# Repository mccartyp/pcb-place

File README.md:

# pcb-place repository

This repository contains complementary command-line tools for reviewable PCB
planning and placement workflows. The architecture separates concerns:
**`pcb-plan` extracts facts, the AI (Claude) generates design intent, and
`pcb-place` executes intent.** A third tool, **`pcb-schgen`**, generates a
readable KiCad schematic (`.kicad_sch`) from a netlist, `board.pln`, and a placed
board — closing the gap where Zener/pcb produces a netlist and PCB but no
schematic.

```text
KiCad PCB + netlist + stackup + board dimensions
  -> pcb-plan inspect       (extract board intelligence -> planning-hints/)
  -> Claude generates board.pln   (authoritative design intent, AI-authored)
  -> pcb-plan check / validate
  -> pcb-plan emit          (board.pln -> placement.ppl)
  -> pcb-place              (deterministic execute -> reports)
  -> Claude optimization loop     (analyze reports, edit board.pln, repeat)
```

- [`pcb-plan`](src/pcb_plan/README.md) is a **board-intelligence extractor** and
  `board.pln` reviewer. Its `inspect` command extracts facts (geometry,
  connectivity) and *candidate hints* (roles, functional paths, power islands,
  edge connectors, mechanicals, RF zones) into a `planning-hints/` directory for
  AI planning. It also reviews, validates (`check`), updates, and emits
  deterministic `placement.ppl` from `board.pln`.
- The AI (Claude) is the **primary planning engine**: it turns `planning-hints/`
  into `board.pln`, the authoritative design-intent document, and iterates on it
  using placement/routing/simulation reports.
- [`pcb-place`](src/pcb_place/README.md) is the **deterministic placement
  executor**. It consumes `placement.ppl`, applies/reflows/optimizes footprint
  placement, validates placement rules, writes placed KiCad `.kicad_pcb` files,
  and reports.
- [`pcb-schgen`](docs/pcb-schgen.md) is the **deterministic schematic
  generator**. It consumes the netlist, the placed board, and `board.pln`, and
  writes a connectivity-correct, readable `.kicad_sch` (local circuits wired,
  rails as power symbols/labels, parts grouped by functional intent) plus a
  generation report and symbol map. It never modifies `pcb-plan`, `pcb-place`,
  or the PCB.

The split is intentional. `pcb-plan inspect` must **not** place components,
create placement ownership, build topology clusters heuristically, or infer a
final floorplan — those are AI planning problems solved in `board.pln`.
`pcb-plan` must not move footprints or route traces; `pcb-place` must not infer
planning strategy, power islands, or a final floorplan. KiCad groups are exported
as metadata only and must never drive placement.

## Repository structure

```text
.
├── README.md                  # Repository overview and structure
├── pyproject.toml             # Packaging and console-script metadata
├── src/
│   ├── pcb_plan/
│   │   ├── README.md          # pcb-plan and board.pln documentation
│   │   ├── __init__.py        # Import package for console scripts
│   │   ├── pcb_plan.py        # pcb-plan implementation
│   │   └── pcb_plan_facades/  # Internal migration/facade modules
│   ├── pcb_place/
│   │   ├── README.md          # pcb-place DSL and executor documentation
│   │   ├── __init__.py        # Import package for console scripts
│   │   └── pcb_place.py       # pcb-place implementation
│   └── pcb_schgen/
│       ├── __init__.py        # Import package for console scripts
│       └── pcb_schgen.py      # pcb-schgen implementation
├── docs/
│   └── pcb-schgen.md          # pcb-schgen documentation
├── examples/                  # Example placement workflows and inputs
└── tests/                     # Unit and CLI integration tests
```

There are no root-level `pcb_plan.py` or `pcb_place.py` compatibility entry
points and no hyphenated tool directories under `src/`. The canonical
executable implementations live beside their READMEs in the importable packages
`src/pcb_plan/` and `src/pcb_place/`, which also provide the normal Python entry
point targets for installed console scripts.

## Overall workflow

`pcb-plan` and `pcb-place` fit after generated board creation and before manual
routing/review:

```text
Zener / Diode pcb design
    ↓
pcb build
    ↓
pcb layout
    ↓
pcb-plan inspect        (extract facts -> planning-hints/)
    ↓
Claude generates board.pln   (AI is the primary planning engine)
    ↓
pcb-plan check          (validate intent)
    ↓
Claude review/optimization
    ↓
pcb-plan emit
    ↓
placement.ppl
    ↓
pcb-place
    ↓
placed KiCad board + reports
    ↓
Claude optimization loop (edit board.pln, repeat)
    ↓
manual high-speed review / routing / DRC
```

A conservative command-line workflow is:

```bash
pcb build board.zen
pcb layout board.zen

# 1. Extract board intelligence into planning-hints/ (facts + candidate hints).
pcb-plan inspect \
  --board layout.kicad_pcb \
  --netlist default.net \
  --width 75 --height 75 \
  --out planning-hints

# 2. Let Claude generate board.pln from planning-hints/ (see planning-hints/
#    ai-pln-prompt.md). board.pln is the authoritative design-intent document:
#    mechanical/edge constraints, regions, power islands, high-speed corridors,
#    functional paths, ownership, routing/SI, stackup, and simulation triggers.
#    The pcb-bootstrap Claude skill drives this step.

# (Legacy heuristic alternative: pcb-plan init writes a first-pass board.pln.)
pcb-plan init \
  --board layout.kicad_pcb \
  --netlist default.net \
  -o board.pln \
  --report-json pcb-plan-init-report.json

# Let Claude review/optimize board.pln before emit. Typical fixes include
# board geometry, regions, keepouts, edge_required/access_side metadata,
# DecouplingArray/PullupArray strategy, differential pairs, routing/SI
# constraints, and OpenEMS/ngspice triggers.

pcb-plan check \
  --pln board.pln \
  --board layout.kicad_pcb \
  --netlist default.net \
  --report-json pcb-plan-check-report.json

# Let Claude review/optimize pcb-plan-check-report.json.

pcb-plan emit \
  --pln board.pln \
  --board layout.kicad_pcb \
  --netlist default.net \
  -o placement.ppl

pcb-place layout.kicad_pcb placement.ppl --dry-run \
  --report-json pcb-place-report.json
# Let Claude review/optimize pcb-place-report.json and feed fixes back to
# board.pln rather than hand-editing placement.ppl when possible.
pcb-place layout.kicad_pcb placement.ppl -o layout.placed.kicad_pcb
pcbnew layout.placed.kicad_pcb
```

Concise AI-assisted workflow:

1. Extract facts and candidate hints with `pcb-plan inspect` into
   `planning-hints/`.
2. Let Claude generate `board.pln` from `planning-hints/` (the authoritative,
   AI-authored design-intent document). The `pcb-bootstrap` skill drives this.
3. Validate intent with `pcb-plan check`, then generate `placement.ppl` with
   `pcb-plan emit`.
4. Apply with `pcb-place` after reviewing the dry-run report.
5. Iterate using placement, routing, DRC/ERC, OpenEMS, and ngspice reports,
   feeding fixes back into `board.pln` (the optimization surface).

Run `pcb-plan check` after `init`/`update` and before `emit` to catch
low-confidence plans (missing nets, mostly-singleton clusters, mostly-unplaced
components, duplicate rules, missing differential pairs, rejected `Series(...)`
inferences, or footprint-extents board geometry) before generating
`placement.ppl`. AI review should prefer `board.pln` intent edits over manual
`placement.ppl` hacks and should preserve provenance for inferred changes. See
[`src/pcb_plan/README.md`](src/pcb_plan/README.md) for the `plan_confidence`
model and the `--strict-confidence`/`--allow-low-confidence` flags on `emit`.

For early use, you can skip the planner and write `placement.ppl` by hand, or
run the planner with only a KiCad board:

```bash
pcb-plan emit --board layout.kicad_pcb -o placement.ppl
pcb-place layout.kicad_pcb placement.ppl -o layout.placed.kicad_pcb
```

When initializing `board.pln` before Edge.Cuts are reliable, pass explicit board geometry so generated regions and edge-aware placements use the intended outline:

```bash
pcb-plan init --board layout.kicad_pcb --width 75 --height 75 -o board.pln
```

Legacy one-shot planner invocation is still supported for compatibility:

```bash
pcb-plan --board layout.kicad_pcb --netlist default.net --intent board.pln -o placement.ppl
```

## Board intelligence extraction: `pcb-plan inspect`

`pcb-plan inspect` is the entry point of the AI planning workflow. It is a
board-intelligence **extractor**, not a floorplanner: it reads facts and emits
*candidate hints* for an AI (or human) to turn into an authoritative
`board.pln`.

```bash
pcb-plan inspect \
  --board layout.kicad_pcb \
  --netlist default.net \
  --width 75 --height 75 \
  --out planning-hints
```

It writes a `planning-hints/` directory:

```text
planning-hints/
  board-hints.json                 # master facts + candidate hints
  board-hints.md                   # human-readable summary
  component-table.csv              # per-component facts (role, bbox, nets)
  connectivity-graph.json          # component/net graph + ownership hints
  footprint-bboxes.json            # bbox, centroid, area per component
  pad-locations.json               # absolute/local pad coordinates and nets
  candidate-functional-paths.json  # connector -> protection -> IC paths
  candidate-power-islands.json     # regulator + hot-loop topology
  candidate-high-speed-paths.json  # high-speed subset of functional paths
  candidate-edge-connectors.json   # access side / auto-rotation / edge_required hints
  candidate-mechanicals.json       # mounting-hole corner assignments
  candidate-rf-zones.json          # RF antenna keepout candidates
  routing-classes.json             # candidate routing classes (impedance needs fab stackup)
  ai-pln-prompt.md                 # prompt to help Claude generate board.pln
  ai-placement-review.md           # checklist for reviewing board.pln vs hints
```

`pcb-plan inspect` must **not** attempt final placement, create topology
clusters heuristically, create placement ownership automatically, or infer a
final floorplan. Everything it emits is a candidate hint and is marked as such.
KiCad groups are exported under `imported_kicad_groups` with `metadata_only:
true` and **must not drive placement** — they are preserved for information only.

`board.pln` is the authoritative design-intent document. It is generated
primarily by AI from `planning-hints/` and contains mechanical constraints,
edge-required components, connector orientation/access sides, placement regions,
power islands, high-speed corridors, functional paths, ownership, routing
classes, SI constraints, stackup, and simulation triggers. The AI optimization
loop primarily edits `board.pln` (preferred), then `placement.ppl` overrides,
then manual `Anchor()` as a last resort. See the
[`pcb-bootstrap`](skills/pcb-bootstrap/SKILL.md) skill for generating it.

## Tool responsibilities

### pcb-plan: extract facts and review intent

`pcb-plan` extracts board intelligence (`inspect`), reviews and validates the
AI-authored `board.pln`, and emits a readable `.ppl` placement plan (`emit`). It
may infer *candidate* roles such as connectors, ICs, decoupling capacitors, ESD
devices, high-speed differential interfaces, RF modules, power regulators,
pullups, and series passives — as hints, not authoritative placement decisions.

`pcb-plan` no longer invents the floorplan: the AI generates `board.pln` from
the hints. `pcb-plan inspect` output and `board.pln` are meant to be reviewed,
AI-optimized, edited, diffed, validated with `check`, and emitted. `pcb-plan`
does **not** place components, route traces, tune differential pairs, validate
impedance, certify EMI behavior, or claim production readiness.

Planner quality depends on real board geometry and connectivity. Explicit
`board.pln` geometry overrides KiCad `Edge.Cuts`, and `Edge.Cuts` overrides the
last-resort footprint-extents fallback. Supplying a netlist lets `pcb-plan` build
multi-member connectivity clusters, infer differential pairs, and place support
passives with semantic helpers such as `Decoupling`, `NearPad`, `ESD`, `Pullup`,
`Series`, `Satellite`, and `Between`; review any `unplaced_components` in the
report.

See [`src/pcb_plan/README.md`](src/pcb_plan/README.md) for planner CLI details,
`board.pln` syntax, provenance, reports, routing/SI hooks, simulation hooks,
heuristics, and limitations.

### pcb-place: execute placement intent

`pcb-place` reads an explicit `.ppl` part-placement file and applies
deterministic footprint-level placement updates to a KiCad `.kicad_pcb` file. It
provides dry-run, check, validation, reporting, alias import, board-geometry
handling, keepout/region validation, and safe atomic writes.

Executor behavior should remain predictable and independent of planner
heuristics. It does **not** infer placement strategy from netlists and does
**not** route traces.

See [`src/pcb_place/README.md`](src/pcb_place/README.md) for the placement DSL,
safety checks, CLI reference, and executor-specific examples.

## Topology-aware placement model

Placement planning and execution follow a fixed priority model:

```text
mechanical constraints first
functional signal path topology second
power topology third
support passives fourth
spacing/clearance always enforced
high-speed/EMI best practices baked into scoring
```

### Groups vs clusters vs ownership

Groups are metadata. A component may belong to several semantic groups at once
(a retimer cluster, an HDMI path, a 1V2 power domain, a decoupling group), but
**final placement ownership is explicit and unique**: exactly one rule owns each
ref's final coordinates. Clusters only preserve coarse neighborhoods; they are
never atomic placement units, and a later higher-priority rule (ESD, power
island member, decoupling array, near-pad) refines members out of the cluster
move. `pcb-plan` reports this as `ownership_model` / `semantic_groups` /
`multi_group_components`; `pcb-place` reports the final winner per ref in
`ownership` and notes every cluster move that a refinement overrode.

Ownership priority (highest first): explicit fixed/locked mechanical,
edge-required connector, explicit anchor, functional-path placement
(ESD/Between/Series), DecouplingArray/NearPad, PullupArray, Satellite, cluster
fallback.

### Mechanical constraints first

Mounting holes are fixed/corner mechanical objects, never cluster members. If
`board.pln` defines `mechanical.mounting_holes`, those corners/locations win;
otherwise `pcb-plan` keeps holes that already sit at distinct corners and
redistributes clustered/colocated holes to distinct corners (`inset` 3 mm) with
a review warning. Board outline, keepouts (RF antenna, cable access), and edge
connectors are planned before any other component.

### Edge-required components

Connectors that leave the board (HDMI, USB, RJ45/Ethernet, DC jacks, card
slots) are inferred — or declared in `board.pln` — as `edge_required`. They are
edge-locked, never pulled inward by optimization, and rotated by access side:

```yaml
components:
  J1:
    role: hdmi_connector
    edge_required: true
    access_side: left
    allow_body_outside_board: true
    locked: true
    rotation: auto
```

`rotation: auto` uses the convention that at rot=0 the footprint's mating face
points toward the top board edge (-y), so auto maps top→0°, right→90°,
bottom→180°, left→270°; supply an explicit rotation when a footprint uses a
different convention. With `allow_body_outside_board: true` the connector body
or courtyard may extend past the board outline (an expected mechanical
condition, not an ordinary outside-board violation) while the footprint anchor
must stay on the board. Support parts stay inside the board unless explicitly
allowed.

### Functional paths and high-speed/EMI scoring

`pcb-plan` builds functional paths from the connectivity graph
(connector → ESD/protection → receiver/retimer) and emits them as
`HighSpeedPath(...)` declarations; `board.pln` `functional_paths:` entries pin
them explicitly. Paths reserve direct corridors before low-speed support parts
are placed: unrelated components are penalized out of corridors during
candidate scoring, and `pcb-place --high-speed-review` writes
`high-speed-placement-review.md` scoring each path for directness/straightness,
flow-through ESD position (protection belongs near the connector), corridor
intruders, and warnings requiring human review.

### Power islands and power/EMI scoring

Regulator sections are planned as topology-aware power islands, not generic
"power component piles": input capacitor tight to the regulator power pins,
inductor and output capacitor compact against the regulator, feedback network
at the FB pin away from the switch node — while downstream load decouplers stay
owned by their loads. `board.pln` `power_islands:` entries pin membership
explicitly. `pcb-place --power-review` writes `power-placement-review.md`
scoring cap/inductor distances, estimated hot-loop area, feedback proximity,
and separation from high-speed paths.

### Spacing profiles

Both tools default to a conservative, non-touching spacing profile and accept a
`board.pln` `spacing:` override:

```yaml
spacing:
  passive_to_passive: 0.25
  passive_to_ic: 0.40
  ic_to_ic: 0.75
  connector_to_component: 1.00
  mechanical_to_component: 1.00
```

Spacing is enforced during candidate scoring and validation. Arrays whose
requested pitch cannot satisfy clearance escalate their spacing instead of
emitting touching parts.

### Stackup profiles

`board.pln` supports reusable stackup templates for 2/4/6/8/10 layers:
`2_layer_basic`, `4_layer_signal_gnd_pwr_signal`, `6_layer_high_speed`,
`8_layer_high_speed`, `10_layer_high_speed`. A bare `stackup: { layers: 6 }`
expands to the conservative 6-layer profile and is marked
`source: stackup_template`, `confidence: medium`, `requires_review: true`.
Templates set layer roles, likely reference planes, and preferred high-speed
layers to improve placement/routing intent only — **controlled impedance always
requires the actual fabricator stackup**, and the tools emit a warning saying
so.

### AI-adjustable .pln and .ppl files

The `.pln` and `.ppl` files are intended to be edited by humans and AI
assistants as part of an iterative layout optimization workflow:

```text
generate board.pln  ->  AI reviews/edits board.pln  ->  pcb-plan emits placement.ppl
->  AI reviews/edits placement.ppl if needed  ->  pcb-place applies placement
->  reports feed back into board.pln
```

Generated files carry stable ordering for diffs, section comments explaining
inferred constraints (effective sides, edge requirements, paths, islands,
arrays), and provenance/`requires_review` markers. Both CLIs emit
`ai-edit-hints.md` (`pcb-plan emit --ai-edit-hints`, `pcb-place
--ai-edit-hints`) listing uncertain placement choices, low-confidence
constraints, multi-group components, placement owners, suggested `.pln`/`.ppl`
edits, and risks requiring engineering review.

### Why human review remains required

Placement-level heuristics and scoring cannot verify impedance, return paths,
reference-plane continuity, plane splits, thermal behavior, RF detuning, or
EMI compliance. The review reports exist to focus engineering attention, not to
replace it.

## Performance and runtime budgets

`pcb-place` uses bounded, staged search so placement stays fast even on dense
boards. A ~100-component board completes in a few seconds in the default
`normal` mode; it never runs unbounded.

### Optimization levels

Choose the search breadth/quality trade-off with `--optimization-level`:

| Level    | Candidates/rule | Reflow depth        | Post-legal probing | Use when |
|----------|-----------------|---------------------|--------------------|----------|
| `fast`   | 150             | local + group only  | accept first legal | quick iteration, CI smoke runs |
| `normal` | 500 (default)   | up to support region| small extra probe  | default placement |
| `deep`   | 2000            | up to parent move   | full search        | debug / exhaustive optimization |

`fast` does no parent reflow and accepts the first legal layout; `normal` is
balanced; `deep` searches harder and reflows more (and is slower by design).

### Time budget and best-effort timeout

`--time-budget-seconds N` (default `60`, `0` disables) bounds wall-clock time.
When the budget expires the placer does **not** abort: it keeps placing the
remaining components with the best known candidate, marks them
`requires_review`, records `timed_out: true`, and continues. Only `--strict`
turns a timeout into a hard error.

```bash
pcb-place board.kicad_pcb placement.ppl \
  --optimization-level normal \
  --time-budget-seconds 60 \
  --max-candidates-per-rule 500 \
  --max-floorplan-iterations 5
```

The placement report includes a `runtime` block:

```json
"runtime": {
  "optimization_level": "normal",
  "elapsed_seconds": 2.17,
  "budget_seconds": 60.0,
  "timed_out": false,
  "candidates_evaluated": 196,
  "cache_hits": 201176,
  "max_candidates_per_rule": 500,
  "degraded_refs": []
}
```

### Spatial index

Collision and clearance checks query a uniform-grid spatial index (stdlib only)
so each candidate is compared against only the handful of footprints near it
instead of every part on the board. The index updates as parts move and is
reported under `spatial_index`:

```json
"spatial_index": {
  "enabled": true,
  "cells": 93,
  "queries": 6382,
  "average_candidates_checked": 0.85
}
```

`average_candidates_checked` stays well below the part count — that is the
difference between local queries and a naive all-pairs scan.

### Bounded, staged search

For each placement primitive the search is bounded and staged:

- **Coarse → fine.** A limited set of high-quality candidates is generated and
  ranked; expensive checks run only on finalists.
- **Pruning.** Candidates that obviously cannot place (outside board/region,
  overlapping the expanded parent bbox, violating a hard keepout) are rejected
  before collision scoring.
- **Early success.** Once an *excellent* legal candidate is found (score under
  the level's threshold), the search stops instead of chasing a marginally
  better one.
- **Caps.** `--max-candidates-per-rule` caps evaluations per primitive so a
  single rule can never explode into thousands of checks. Legality always wins
  over the cap: the spacing-escalation ladder is never cut short before a legal
  placement is found.

### Reflow levels

Reflow is local by default, escalating only as needed (low-priority blockers —
testpoints, LEDs, straps, pullups, passives — move before critical parts; edge-
required and mechanically locked parts never move):

```text
level 0  local primitive only
level 1  same array/group
level 2  same parent support region
level 3  same functional island/path
level 4  adjacent regions
level 5  parent IC movement
```

`fast` uses levels 0–2, `normal` 0–3 (parent movement only when local placement
is impossible and the parent is movable), `deep` 0–5.

### Profiling

`--profile-placement profile.json` writes per-rule runtime, candidate counts,
collision-check counts, spatial-index stats, cache hit/miss, reflow attempts,
and the slowest rules — the data needed to tune a slow board:

```bash
pcb-place board.kicad_pcb placement.ppl --profile-placement profile.json
```

### Progress output

`--progress` prints concise, throttled per-rule progress to stderr for long
runs, e.g. `placing 34/102 C19 DecouplingArray candidates=120 elapsed=8.2s`.

## Installation

From the repository root:

```bash
pip install .
```

For development:

```bash
pip install -e '.[dev]'
pytest
```

The installed console scripts are:

```bash
pcb-plan --help
pcb-place --help
pcb-schgen --help
```

## Safety model

Both tools are sidecars around KiCad files:

- `pcb-plan` never writes directly to `.kicad_pcb`; it reads or writes
  `board.pln`, emits `placement.ppl`, and can emit JSON/Markdown reports plus
  routing/simulation planning artifacts.
- `pcb-place` rewrites only matched footprint-level placement records and
  defaults to writing a separate output file unless `--in-place` is explicitly
  requested.
- Generated or executed placement must be reviewed in KiCad before routing and
  fabrication.
- High-speed routing, impedance, return paths, reference planes, DRC/ERC,
  manufacturability, thermal behavior, RF behavior, and EMI compliance remain
  engineering responsibilities.

## Documentation map

- [`src/pcb_plan/README.md`](src/pcb_plan/README.md): planner-specific
  documentation for `board.pln`, lifecycle commands, routing/SI constraints,
  simulation hooks, reports, and `.ppl` generation.
- [`src/pcb_place/README.md`](src/pcb_place/README.md): executor-specific
  documentation for applying `.ppl` files to KiCad boards.
- [`docs/pcb-schgen.md`](docs/pcb-schgen.md): `pcb-schgen` schematic-generation
  CLI, inputs, wire-vs-label policy, reports, and KiCad compatibility.
- [`examples/`](examples): example placement workflows and input files.
- [`tests/`](tests): unit and CLI integration tests for both tools.

## Claude Skills

[`skills/`](skills) contains Claude Code skills that teach Claude how to drive
this repository's tools:

- [`skills/pcb-plan/SKILL.md`](skills/pcb-plan/SKILL.md) — `board.pln` and
  `placement.ppl` lifecycle: init, AI-assisted optimization, check, review,
  explain, update, emit, routing/SI constraints, stackup, differential pairs,
  simulation hooks, provenance.
- [`skills/pcb-place/SKILL.md`](skills/pcb-place/SKILL.md) — applying and
  debugging `placement.ppl` against a `.kicad_pcb` board: dry-run report
  review, validation, collisions/spacing/keepouts/regions, array diagnostics,
  edge-required movement attempts, troubleshooting.
- [`skills/pcb-automation-orchestrator/SKILL.md`](skills/pcb-automation-orchestrator/SKILL.md) —
  end-to-end AI iteration across `pcb-plan`, `pcb-place`, routing, DRC/ERC,
  and optional OpenEMS/ngspice simulation, including review, assisted, and
  bounded autonomous modes plus all-net and high-speed routing modes.

Short workflow: generate `board.pln`, let Claude review/optimize it, generate
`placement.ppl`, apply with `pcb-place`, and iterate using reports. Use
`pcb-plan` to own `board.pln`, use `pcb-place` to apply/debug the emitted
`placement.ppl` against a KiCad board, and use `pcb-automation-orchestrator`
to coordinate the full init/check/edit/emit/place/route/verify/simulate/update
loop. See [`skills/README.md`](skills/README.md) for details on when to use
each.

### Placement regions, support arrays, and edge-required parts

`pcb-place` models grouped support-part placement with an internal `PlacementRegion`: a legal strip on the left, right, top, or bottom of the expanded parent footprint bbox, clipped to board bounds and any strict `Region(...)` requested by the rule. `DecouplingArray(...)` and `PullupArray(...)` use these regions for capacity planning before selecting a scored candidate.

For arrays near a board edge, pcb-place computes the full array bounding box and slides it along the side tangent before rejecting it. Top/bottom arrays slide in X; left/right arrays slide in Y. Placement search reports include `placement_region`, capacity fields, `original_array_bbox`, `slid_array_bbox`, `slide_applied`, `slide_dx`, and `slide_dy`. Use `--explain-placement REF` to print the recorded winning score, candidate regions, slide data, and top rejected candidates for a specific part.

Board, region, keepout, and coordinate geometry accepts integral or floating-point values. For example, `Board(width=75, height=75)` and `Board(width=75.0, height=75.0)` are equivalent internally.

Edge-access components can be declared with metadata such as `edge_required=True`, `mechanical=True`, `locked=True`, and `access_side="left"` on `Edge(...)` placements. Edge-required anchors are treated as locked/high-priority owners; support components must move around them instead of pulling the connector or mechanical body inward. The generated report lists `edge_required_refs` separately from other locked refs.

Placement ownership precedence is enforced by priority and locking: fixed/locked/edge-required placements win over explicit anchors, pin-aware arrays, near-pad/satellite rules, and cluster fallback. When a cluster gives a coarse placement and a later DecouplingArray/PullupArray refines a support part, diagnostics report the refinement rather than silently fighting the rules.

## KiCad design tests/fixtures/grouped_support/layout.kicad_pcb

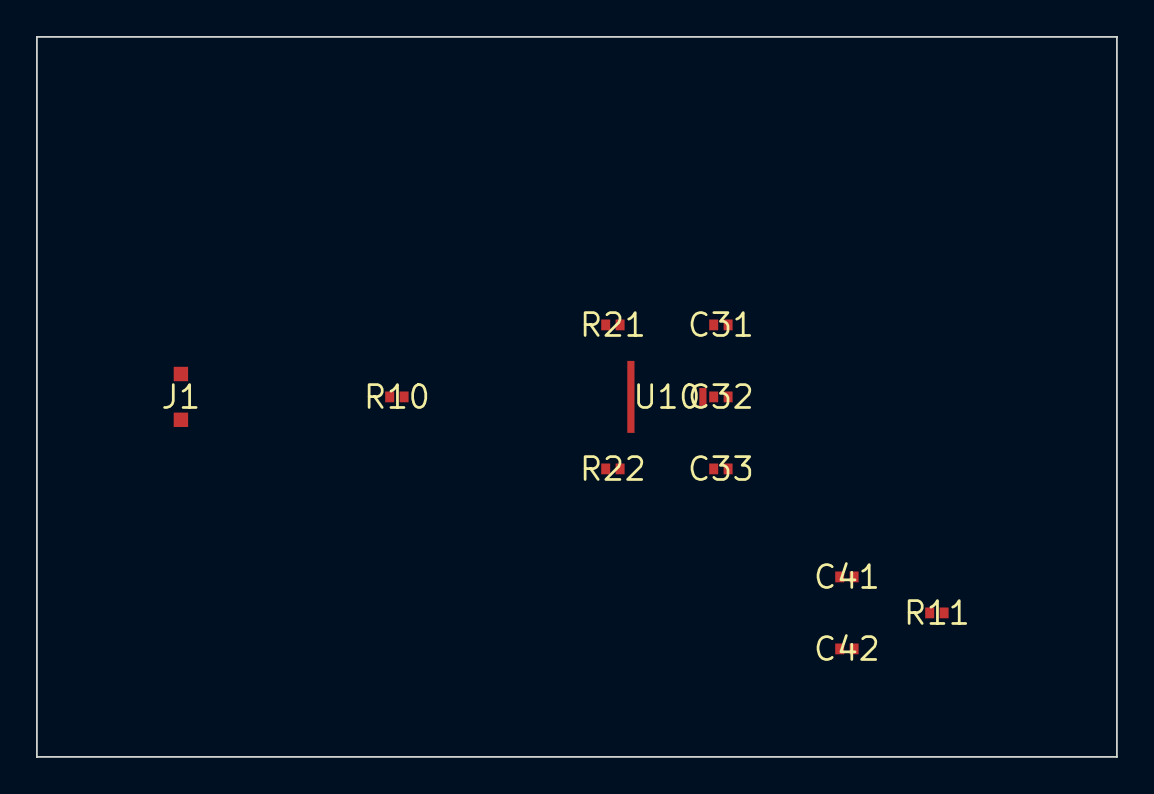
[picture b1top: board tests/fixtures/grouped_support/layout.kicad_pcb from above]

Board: 0 copper layers, 60.0 x 40.0 mm, 11 parts (0 on the bottom side), 8 nets, no tracks yet.

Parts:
C31, C32, C33: 100nF; C_0402
C41, C42: 1uF; C_0402
J1: CONN; PinHeader_1x02
R10: 33; R_0402
R11: 100; R_0402
R21, R22: 10k; R_0402
U10: MCU; QFN-40

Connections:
3V3: C31.1, C32.1, C33.1, R21.1, R22.1, U10.1
DATA: J1.1, R10.1
DATA2: R10.2, U10.5
FNET1: C41.1, R11.1
FNET2: C42.1, R11.2
GND: C31.2, C32.2, C33.2, J1.2, U10.2
SCL: R22.2, U10.4
SDA: R21.2, U10.3

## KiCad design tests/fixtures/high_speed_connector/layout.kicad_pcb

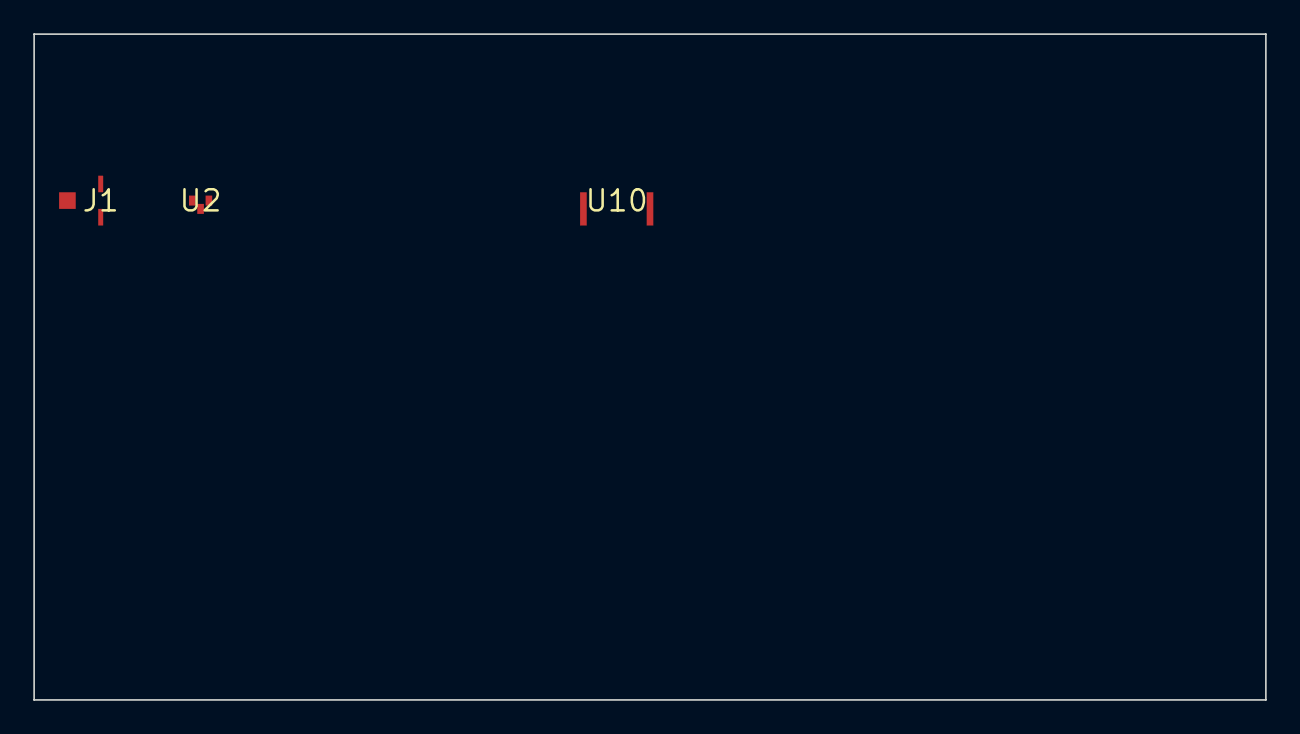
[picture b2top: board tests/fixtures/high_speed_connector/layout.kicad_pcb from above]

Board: 0 copper layers, 74.0 x 40.0 mm, 3 parts (0 on the bottom side), 3 nets, no tracks yet.

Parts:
J1: HDMI_IN; HDMI_A
U2: ESD; ESD_Array
U10: HDMI Retimer; QFN-40

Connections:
GND: J1.G, U2.3, U10.4
TMDS0_N: J1.2, U2.2, U10.2
TMDS0_P: J1.1, U2.1, U10.1

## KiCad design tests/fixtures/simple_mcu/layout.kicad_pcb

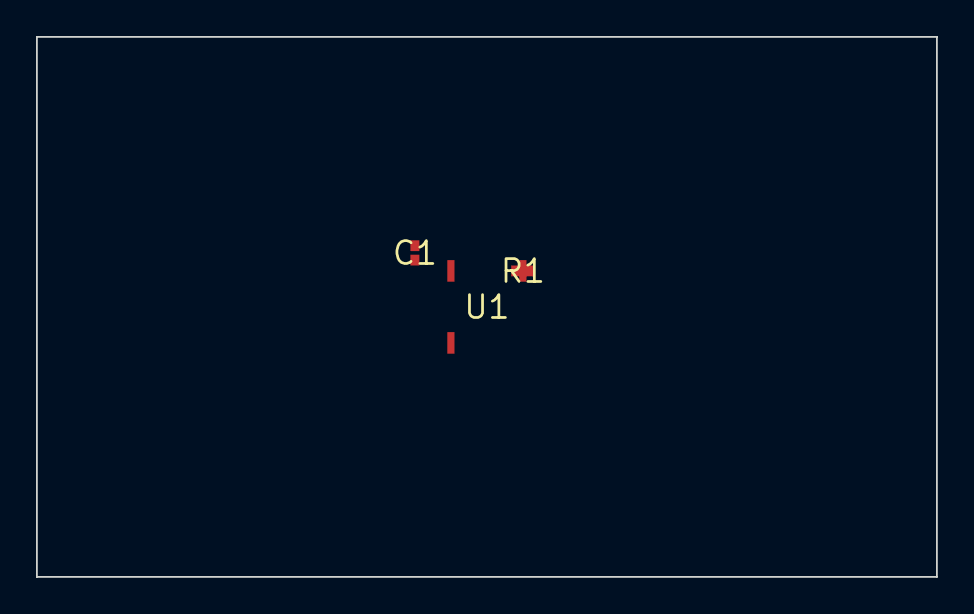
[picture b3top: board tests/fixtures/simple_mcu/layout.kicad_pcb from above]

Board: 0 copper layers, 50.0 x 30.0 mm, 3 parts (0 on the bottom side), 3 nets, no tracks yet.

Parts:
C1: 100nF; C_0402
R1: 10k; R_0402
U1: MCU; TQFP-32

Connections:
3V3: C1.1, R1.1, U1.1
BOOT0: R1.2, U1.3
GND: C1.2, U1.2

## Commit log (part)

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2026-06-10 Add Zener netlist alias resolution
2026-06-10 Filter suffix alias matches to existing footprints
2026-06-10 Make KiCad placement output safer
2026-06-10 Let dry-runs report unsafe placements
2026-06-10 Add board geometry and outline support
2026-06-10 Validate rectangular Edge.Cuts outlines
2026-06-11 Fix collision validation scope and board side handling
2026-06-11 Ensure tests include KiCad PCB fixture
2026-06-11 Include examples in source distribution
2026-06-11 Restore all minimal test fixtures when missing
2026-06-11 Fix generated UUID handling
2026-06-11 Deduplicate resolved cluster members
2026-06-11 Add planner-friendly placement primitives
2026-06-11 Honor planner placement overrides during search
2026-06-11 Document pln syntax reference
2026-06-11 Avoid overlapping synthesized RF keepouts
2026-06-11 Remove root compatibility entry points
2026-06-11 Add Claude skills for pcb-plan, pcb-place, and orchestrator workflows
    Adds skills/pcb-plan, skills/pcb-place, and
    skills/pcb-automation-orchestrator SKILL.md files plus skills/README.md,
    and links them from the root README under a new Claude Skills section.
    https://claude.ai/code/session_01GYvjSuXui5PLRL4NxjSqD3
2026-06-11 Standardize src package directory names
2026-06-11 Fix connector cluster edge-placement heuristic and Edge() top/bottom offset
    Edge() ignored y=/offset= for top/bottom edges, collapsing connectors
    placed on the same edge to a single point. The connector cluster
    heuristic also only distinguished left/right thirds of the board,
    never producing top/bottom edge placements, and force-snapped interior
    connectors to an edge even when that introduced large relocations or
    new overlaps. Pick the nearest of all four edges, only snap to an edge
2026-06-11 Make pcb-plan connectivity-aware
2026-06-12 Add search-based placement engine for robust NearPad/Satellite/Between
    Replace immediate-failure logic in NearPad, Satellite, Between, and
    cluster member placement with a generic candidate search engine that
    scores nearby legal positions by distance, clearance margin, and board
    edge proximity before giving up. Adds side="inward" for NearPad,
    alternate-side/perimeter search for Satellite, auto_spread for Between,
    cluster-local region search for soft members, a DecouplingArray()
2026-06-12 Add DecouplingArray/PullupArray primitives, pcb-plan check, and plan confidence gates
    pcb-place gains place_array_near_target() and the DecouplingArray()/
    PullupArray() primitives, which place a group of related parts as a
    single row near a parent (or pad), trying candidate sides, keeping the
    group together when it fits, and falling back to per-member
    search-based placement with diagnostics otherwise.
    pcb-plan now emits a single DecouplingArray()/PullupArray() rule for
2026-06-12 Add .gitignore for Python bytecode caches
2026-06-12 Fix decoupling array parent keepout placement
2026-06-12 Add scored placement candidate selection
2026-06-12 Add pcb-plan init board geometry options
2026-06-12 Slide arrays within strict placement regions
2026-06-12 docs: add AI-assisted pcb plan optimization workflow
2026-06-12 Make pcb-plan cluster member inference smarter, emit Edge.Cuts outline
    - Exclude power-net (not just ground-net) connectivity when pulling
    components into a cluster, so shared power rails no longer balloon
    cluster membership to nearly the whole board.
    - Cap all proximity-based and connectivity-based membership checks to
    the cluster radius so electrically-related but physically distant
    components aren't dragged into a rigidly-moved cluster.
2026-06-12 Gate emit_outline on trusted board geometry; require electrical link for connector cluster support parts
    emit_outline=True is no longer emitted when board geometry was inferred
    from footprint extents (low confidence), avoiding a synthetic Edge.Cuts
    outline that could cut through components. For connector clusters
    (proximity_any_role=False), nearby support-role passives are only swept
    into the rigidly-moved Edge() cluster if they share a signal/connection
    with the connector, preventing unrelated decoupling caps from being
2026-06-12 Redesign pcb-plan/pcb-place for topology-aware floorplanning and ownership
    Placement now follows a fixed priority model: mechanical constraints first,
    functional signal-path topology second, power topology third, support
    passives fourth, with spacing always enforced and high-speed/EMI practices
    baked into scoring.
    pcb-plan:
    - Mounting holes are fixed mechanical objects distributed to distinct
2026-06-13 Add constraint-driven iterative floorplanner with reflow and no-abort placement
    Treat a local placement failure as evidence the floorplan is suboptimal
    rather than a component problem. pcb-place now runs an iterative
    floorplanner that places, scores the global layout, reflows the worst
    constraints, and re-scores until convergence.
    Reflow ladder (before parking):
    - repack within the grouped-array search (existing)
2026-06-13 Route all primitive search failures through no-abort parking; demote parked validation
    Address two P1 review findings on the no-abort guarantee:
    1. NearPad / Satellite(side="auto") / Between performed their own candidate
    searches and raised PlacementError directly, bypassing reflow/parking. They
    now share _resolve_unplaceable_search(), which tries a Level-2 reflow and
    otherwise parks, so default best-effort placement no longer aborts on these
    primitives. Only strict/fail-fast raise.
2026-06-13 Fix board geometry regressions in pcb-plan and pcb-place
    Restore robust board geometry handling across the floorplanner:
    - Footprint-extents fallback now uses footprint bounding boxes (with a
    per-footprint at-position fallback) plus a 5 mm margin, so valid
    footprints never collapse to a zero-size board. Adds
    footprint_extents_bounds()/_footprint_abs_bbox() and a configurable
    margin (DEFAULT_FOOTPRINT_MARGIN_MM).
2026-06-13 Keep footprint-extents fallback invalid when there are no footprints
    Address review feedback: when a board has neither Edge.Cuts nor any
    parseable footprints, the 5 mm margin previously fabricated a valid-looking
    10x10 footprint_extents board that passed validation. The "never zero"
    guarantee only applies to valid footprints, so the empty case now stays
    zero-size and is rejected with the clear sourced error.
    - infer_geometry_from_footprints() returns zero-size geometry (no margin)
2026-06-13 Add bounded, staged placement search with spatial indexing and runtime budgets
    Placement runtime is now bounded and predictable: a ~100-component board that
    previously took minutes (and could approach 30+ minutes on dense layouts) now
    completes in a few seconds in the default normal mode.
    Core changes (pcb-place):
    - Spatial index: a stdlib uniform-grid index over placed footprint bboxes.
    Collision and clearance checks query only nearby parts instead of scanning
2026-06-13 Honor strict timeouts during searches
2026-06-13 Honor strict timeouts during searches
    ### Motivation
    - In strict mode a run that observes the budget expire during an expensive mid-search (e.g. grouped-array probing) only set `timed_out` and continued until the next rule, allowing a run to complete s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
    - Make timeout behavior consistent so any search path that detects an expired `RuntimeBudget` immediately raises when `strict=True`.
    ### Description
    - Add a shared helper method `PlacementEngine._raise_strict_timeout()` that raises a `PlacementError` when `self.runtime.strict` and the budget has expired.
    - Call the helper from `PlacementEngine._maybe_degrade_on_timeout()` to pres
2026-06-13 Clamp cluster member targets to board bounds
2026-06-13 Honor outside-board opt-out for cluster clamping
2026-06-13 Reduce CLI wrapper merge surface
2026-06-13 Avoid edge cluster support overlaps
2026-06-13 Avoid edge cluster support overlaps
    ### Motivation
    - Cluster moves previously attempted to drag locked non-anchor members and could place support parts on top of each other when an anchor was edge-required/locked, causing validation overlap errors.
    - The change aims to preserve explicit locked placements and to cause support parts in edge-required/locked clusters to spread to legal, non-overlapping locations.
    ### Description
    - In `src/pcb_place/pcb_place.py` the cluster placement loop now skips moving non-anchor members that are already locked, records a `locked_move_attempt`, and emits a warning message instead of attem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
    - The cluster placement now computes an `avoid_ov
2026-06-13 Avoid overlaps in cluster support placements
2026-06-14 Avoid overlaps for non-anchor cluster members and honor --allow-overlap
    ### Motivation
    - Cluster support parts that were listed alongside their anchor could remain coincident/overlapped even when global placement avoidance was enabled, causing validation failures for overlapping origin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
    ### Description
    - Add a `permissive_overlap` flag to `PlacementEngine` and wire it from the `allow_overlap` CLI/application option so `--allow-overlap` still relaxes avoidance when requested.\
    - Change cluster-placement logic so non-anchor members use the placement policy (`PlacementPolicy(avoid_overlap=True)`) to decide overlap avoi
2026-06-14 Floorplanner: fix vertical-edge span and honor keepouts
    Addresses two P1 review findings:
    - _edge_span used the board width for left/right edges, but connectors there
    are distributed along y, so the span must be the board height (and width for
    top/bottom). On a rectangular board this produced along-edge coordinates off
    the board; square boards masked it. Swap the dimensions.
    - compute_floorplan ignored declared keepouts, so the force-directed solve
2026-06-14 Floorplanner: handle tight boards and circular cluster membership
    Follow-up to the wirelength-driven floorplanner for smaller boards.
    - Split real-body (hard) extents from halo-inflated (soft) extents. The soft
    halo spreads parts for their support arrays when there is room; the hard
    pass guarantees real-footprint + clearance separation that pcb-place
    validates. Clamp parts by their real body so they can use the whole core.
    - Add a decompaction fallback: any part the pairwise relaxation wedges against
2026-06-14 Add pcb-plan inspect; pivot to extract -> AI plan -> execute architecture
    Convert pcb-plan from a heuristic floorplanner into a board-intelligence
    extractor that feeds AI-driven board.pln generation.
    - Add `pcb-plan inspect` command that writes a planning-hints/ directory of
    facts and candidate hints (board-hints.json/.md, component-table.csv,
    connectivity-graph.json, footprint-bboxes.json, pad-locations.json,
    candidate-{functional-paths,power-islands,high-speed-paths,edge-connectors,
2026-06-14 inspect: honor unsupported --stackup-layers instead of silent fallthrough
    When --stackup-layers is a valid count with no built-in template (e.g. 12),
    preserve the requested layer count with a no-template profile flagged
    requires_review, and emit a board-hints warning, instead of silently falling
    back to the 4/2-layer heuristic and contradicting the explicit input.
    https://claude.ai/code/session_01S4xduru4BPBP2uhyXbNvye
